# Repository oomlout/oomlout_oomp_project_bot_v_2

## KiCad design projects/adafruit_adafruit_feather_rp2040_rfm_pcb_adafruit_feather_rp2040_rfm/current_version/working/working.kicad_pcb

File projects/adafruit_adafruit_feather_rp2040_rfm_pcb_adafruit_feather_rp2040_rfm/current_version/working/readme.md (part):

# adafruit_feather_rp2040_rfm_pcb
 
## summary 
* id: adafruit_adafruit_feather_rp2040_rfm_pcb_adafruit_feather_rp2040_rfm
* user: adafruit
* name: adafruit_feather_rp2040_rfm_pcb
* board: adafruit_feather_rp2040_rfm
* repo: https://github.com/adafruit/Adafruit-Feather-RP2040-RFM-PCB

* src_file_repo_sch: 
* src_file_repo_sch_link: https://github.com/adafruit/Adafruit-Feather-RP2040-RFM-PCB/tree/main/
* full details link: https://github.com/oomlout/oomlout_oomp_project_bot_v_2/tree/main/projects/adafruit_adafruit_feather_rp2040_rfm_pcb_adafruit_feather_rp2040_rfm/current_version/working  

## schematic  
  
[schematic (pdf)](working_schematic.pdf) 

## pcb  

[board (pdf)](working.pdf)  

## working_bom
| Id | Designator | Footprint | Quantity | Designation | Supplier and ref |  | None | 
| --- | --- | --- | --- | --- | --- | --- | --- | 
| 1 | PLABEL18 | PLABEL18 | 1 |  |  |  | [''] | 
| 2 | C13,C9,C12,C6,C18,C7,C14 | _0402NO | 7 | 0.1uF |  |  | [''] | 
| 3 | Y1 | CRYSTAL_2.5X2 | 1 | 12MHz/12pF |  |  | [''] | 
| 4 | PLABEL19 | PLABEL19 | 1 |  |  |  | [''] | 
| 5 | L0 | CHIPLED_0603_NOOUTLINE | 1 | RED |  |  | [''] | 
| 6 | R11,R6 | _0402NO | 2 | 1K |  |  | [''] | 
| 7 | CHG0 | CHIPLED_0603_NOOUTLINE | 1 | ORANGE |  |  | [''] | 
| 8 | U1 | USON8_4X4 | 1 | 8MB QSPI |  |  | [''] | 
| 9 | PLABEL8 | PLABEL8 | 1 |  |  |  | [''] | 
| 10 | LED1 | SK6805_1515 | 1 | WS2812B_SK6805_1515 |  |  | [''] | 
| 11 | PLABEL2 | PLABEL2 | 1 |  |  |  | [''] | 
| 12 | R14,R15,R3,R2,R4,R7,R1,R5 | _0402NO | 8 | 10K |  |  | [''] | 
| 13 | PLABEL7 | PLABEL7 | 1 |  |  |  | [''] | 
| 14 | PLABEL4 | PLABEL4 | 1 |  |  |  | [''] | 
| 15 | R12,R13,R8 | _0402NO | 3 | 5.1K |  |  | [''] | 
| 16 | U2 | SOT23-5 | 1 | RT9080-3.3 |  |  | [''] | 
| 17 | PLABEL0 | PLABEL0 | 1 |  |  |  | [''] | 
| 18 | X1 | JSTPH2_BATT | 1 | JSTPH |  |  | [''] | 
| 19 | @HOLE0,@HOLE1 |  | 2 |  |  |  | [''] | 
| 20 | SW2,SW1 | BTN_RKB2_4.6X2.8 | 2 | KMR2 |  |  | [''] | 
| 21 | D4 | SOD-323F | 1 | PMEG2020AEA |  |  | [''] | 
| 22 | X6 | USB_C_CUSB31-CFM2AX-01-X | 1 | USB Type C |  |  | [''] | 
| 23 | C4,C20,C1,C5 | 0805-NO | 4 | 10uF |  |  | [''] | 
| 24 | U$31,U$32 | MOUNTINGHOLE_2.5_PLATED | 2 | MOUNTINGHOLE2.5 |  |  | [''] | 
| 25 | U3 | SOT23-5 | 1 | MCP73831T-2ACI/OT |  |  | [''] | 
| 26 | PLABEL16 | PLABEL16 | 1 |  |  |  | [''] | 
| 27 | PLABEL1 | PLABEL1 | 1 |  |  |  | [''] | 
| 28 | C8,C10,C15,C11,C17 | _0402NO | 5 | 1uF |  |  | [''] | 
| 29 | PLABEL5 | PLABEL5 | 1 |  |  |  | [''] | 
| 30 | PLABEL21 | PLABEL21 | 1 |  |  |  | [''] | 
| 31 | U$34,U$35 | FIDUCIAL_1MM | 2 | FIDUCIAL_1MM |  |  | [''] | 
| 32 | JP3 | 1X12_ROUND | 1 |  |  |  | [''] | 
| 33 | PLABEL22 | PLABEL22 | 1 |  |  |  | [''] | 
| 34 | PLABEL11 | PLABEL11 | 1 |  |  |  | [''] | 
| 35 | C3,C2 | _0402NO | 2 | 22pF |  |  | [''] | 
| 36 | PLABEL3 | PLABEL3 | 1 |  |  |  | [''] | 
| 37 | PLABEL6 | PLABEL6 | 1 |  |  |  | [''] | 
| 38 | PLABEL14 | PLABEL14 | 1 |  |  |  | [''] | 
| 39 | RFM1 | RFMHCW_SMT | 1 | RFM9x |  |  | [''] | 
| 40 | X2 | U.FL | 1 | uFL |  |  | [''] | 
| 41 | R10,R9 | _0402NO | 2 | 22 ohm |  |  | [''] | 
| 42 | JP1 | 1X16_ROUND | 1 |  |  |  | [''] | 
| 43 | PLABEL17 | PLABEL17 | 1 |  |  |  | [''] | 
| 44 | Q3 | DFN2015-3 | 1 | DMG3415UFY |  |  | [''] | 
| 45 | CONN1 | JST_SH4_RA | 1 | STEMMA_I2C_QTRA |  |  | [''] | 
| 46 | PLABEL12 | PLABEL12 | 1 |  |  |  | [''] | 
| 47 | PLABEL15 | PLABEL15 | 1 |  |  |  | [''] | 
| 48 | PLABEL20 | PLABEL20 | 1 |  |  |  | [''] | 
| 49 | PLABEL10 | PLABEL10 | 1 |  |  |  | [''] | 
| 50 | PLABEL9 | PLABEL9 | 1 |  |  |  | [''] | 
| 51 | PLABEL13 | PLABEL13 | 1 |  |  |  | [''] | 
| 52 | D3 | SOD-323F | 1 | 1N4148 |  |  | [''] | 
| 53 | JP4 | 1X01_ROUND | 1 |  |  |  | [''] | 
| 54 | IC1 | QFN56_7MM_REDUCEDEPAD | 1 | RP2040_QFN56 |  |  | [''] | 
| 55 | PLABEL25 | PLABEL25 | 1 |  |  |  | [''] | 
| 56 | PLABEL35 | PLABEL35 | 1 |  |  |  | [''] | 
| 57 | PLABEL53 | PLABEL53 | 1 |  |  |  | [''] | 
| 58 | PLABEL40 | PLABEL40 | 1 |  |  |  | [''] | 
| 59 | PLABEL45 | PLABEL45 | 1 |  |  |  | [''] | 
| 60 | U$46 | STEMMAQT | 1 |  |  |  | [''] | 
| 61 | U$47 | FEATHERLOGO_SMALL | 1 |  |  |  | [''] | 
| 62 | PLABEL47 | PLABEL47 | 1 |  |  |  | [''] | 
| 63 | PLABEL24,PLABEL54 | PLABEL24 | 2 |  |  |  | [''] | 
| 64 | PLABEL46 | PLABEL46 | 1 |  |  |  | [''] | 
| 65 | PLABEL33 | PLABEL33 | 1 |  |  |  | [''] | 
| 66 | PLABEL52 | PLABEL52 | 1 |  |  |  | [''] | 
| 67 | PLABEL49 | PLABEL49 | 1 |  |  |  | [''] | 
| 68 | PLABEL27 | PLABEL27 | 1 |  |  |  | [''] | 
| 69 | PLABEL540 | PLABEL540 | 1 |  |  |  | [''] | 
| 70 | PLABEL32 | PLABEL32 | 1 |  |  |  | [''] | 
| 71 | PLABEL30 | PLABEL30 | 1 |  |  |  | [''] | 
| 72 | PLABEL38 | PLABEL38 | 1 |  |  |  | [''] | 
| 73 | PLABEL41 | PLABEL41 | 1 |  |  |  | [''] | 
| 74 | PLABEL44 | PLABEL44 | 1 |  |  |  | [''] | 
| 75 | PLABEL34 | PLABEL34 | 1 |  |  |  | [''] | 
| 76 | PLABEL29 | PLABEL29 | 1 |  |  |  | [''] | 
| 77 | PLABEL51 | PLABEL51 | 1 |  |  |  | [''] | 
| 78 | PLABEL36 | PLABEL36 | 1 |  |  |  | [''] | 
| 79 | PLABEL42 | PLABEL42 | 1 |  |  |  | [''] | 
| 80 | PLABEL39 | PLABEL39 | 1 |  |  |  | [''] | 
| 81 | PLABEL43 | PLABEL43 | 1 |  |  |  | [''] | 
| 82 | U$13 | PCBFEAT-REV-040 | 1 |  |  |  | [''] | 
| 83 | U$45 | ADAFRUIT_5MM | 1 |  |  |  | [''] | 
| 84 | PLABEL31 | PLABEL31 | 1 |  |  |  | [''] | 
| 85 | PLABEL26 | PLABEL26 | 1 |  |  |  | [''] | 
| 86 | D-1,D+1 | B1,27 | 2 | TPB1,27 |  |  | [''] | 
| 87 | PLABEL28 | PLABEL28 | 1 |  |  |  | [''] | 
| 88 | PLABEL48 | PLABEL48 | 1 |  |  |  | [''] | 
| 89 | PLABEL37 | PLABEL37 | 1 |  |  |  | [''] | 
| 90 | TP3 | TESTPOINT_ROUND_1.5MM_NO | 1 |  |  |  | [''] | 
| 91 | PLABEL23 | PLABEL23 | 1 |  |  |  | [''] | 

## bom_schematic
| Ref | Qnty | Value | Cmp name | Footprint | Description | Vendor | DNP | 
| --- | --- | --- | --- | --- | --- | --- | --- | 
| C1, C4, C5, C20 | 4 | 10uF | CAP_CERAMIC0805-NOOUTLINE | working:0805-NO |  |  |  | 
| C2, C3 | 2 | 22pF | CAP_CERAMIC_0402NO | working:_0402NO |  |  |  | 
| C6, C7, C9, C12, C13, C14, C18 | 7 | 0.1uF | CAP_CERAMIC_0402NO | working:_0402NO |  |  |  | 
| C8, C10, C11, C15, C17 | 5 | 1uF | CAP_CERAMIC_0402NO | working:_0402NO |  |  |  | 
| CHG0 | 1 | ORANGE | LED0603_NOOUTLINE | working:CHIPLED_0603_NOOUTLINE |  |  |  | 
| CONN1 | 1 | STEMMA_I2C_QTRA | STEMMA_I2C_QTRA | working:JST_SH4_RA |  |  |  | 
| D3 | 1 | 1N4148 | DIODESOD-323F | working:SOD-323F |  |  |  | 
| D4 | 1 | PMEG2020AEA | DIODESOD-323F | working:SOD-323F |  |  |  | 
| D+1 | 1 | TPB1,27 | TPB1,27 | working:B1,27 |  |  |  | 
| D-1 | 1 | TPB1,27 | TPB1,27 | working:B1,27 |  |  |  | 
| IC1 | 1 | RP2040_QFN56 | RP2040_QFN56 | working:QFN56_7MM_REDUCEDEPAD |  |  |  | 
| JP1 | 1 | HEADER-1X16ROUND | HEADER-1X16ROUND | working:1X16_ROUND |  |  |  | 
| JP3 | 1 | HEADER-1X12 | HEADER-1X12 | working:1X12_ROUND |  |  |  | 
| JP4 | 1 | HEADER-1X1ROUND | HEADER-1X1ROUND | working:1X01_ROUND |  |  |  | 
| L0 | 1 | RED | LED0603_NOOUTLINE | working:CHIPLED_0603_NOOUTLINE |  |  |  | 
| LED1 | 1 | WS2812B_SK6805_1515 | WS2812B_SK6805_1515 | working:SK6805_1515 |  |  |  | 
| Q3 | 1 | DMG3415UFY | MOSFET-P_DFN2015 | working:DFN2015-3 |  |  |  | 
| R1, R2, R3, R4, R5, R7, R14, R15 | 8 | 10K | RESISTOR_0402NO | working:_0402NO |  |  |  | 
| R6, R11 | 2 | 1K | RESISTOR_0402NO | working:_0402NO |  |  |  | 
| R8, R12, R13 | 3 | 5.1K | RESISTOR_0402NO | working:_0402NO |  |  |  | 
| R9, R10 | 2 | 22 ohm | RESISTOR_0402NO | working:_0402NO |  |  |  | 
| RFM1 | 1 | RFM9x | RFM69HCW_SMT | working:RFMHCW_SMT |  |  |  | 
| SW1, SW2 | 2 | KMR2 | SWITCH_TACT_SMT_RKB2 | working:BTN_RKB2_4.6X2.8 |  |  |  | 
| TP3 | 1 | TESTPOINTROUND1.5MMNO | TESTPOINTROUND1.5MMNO | working:TESTPOINT_ROUND_1.5MM_NO |  |  |  | 
| U1 | 1 | 8MB QSPI | SPIFLASH_8PIN_4X4 | working:USON8_4X4 |  |  |  | 
| U2 | 1 | RT9080-3.3 | VREG_SOT23-5 | working:SOT23-5 |  |  |  | 
| U3 | 1 | MCP73831T-2ACI/OT | MCP73831/2 | working:SOT23-5 |  |  |  | 
| U$31, U$32 | 2 | MOUNTINGHOLE2.5 | MOUNTINGHOLE2.5 | working:MOUNTINGHOLE_2.5_PLATED |  |  |  | 
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
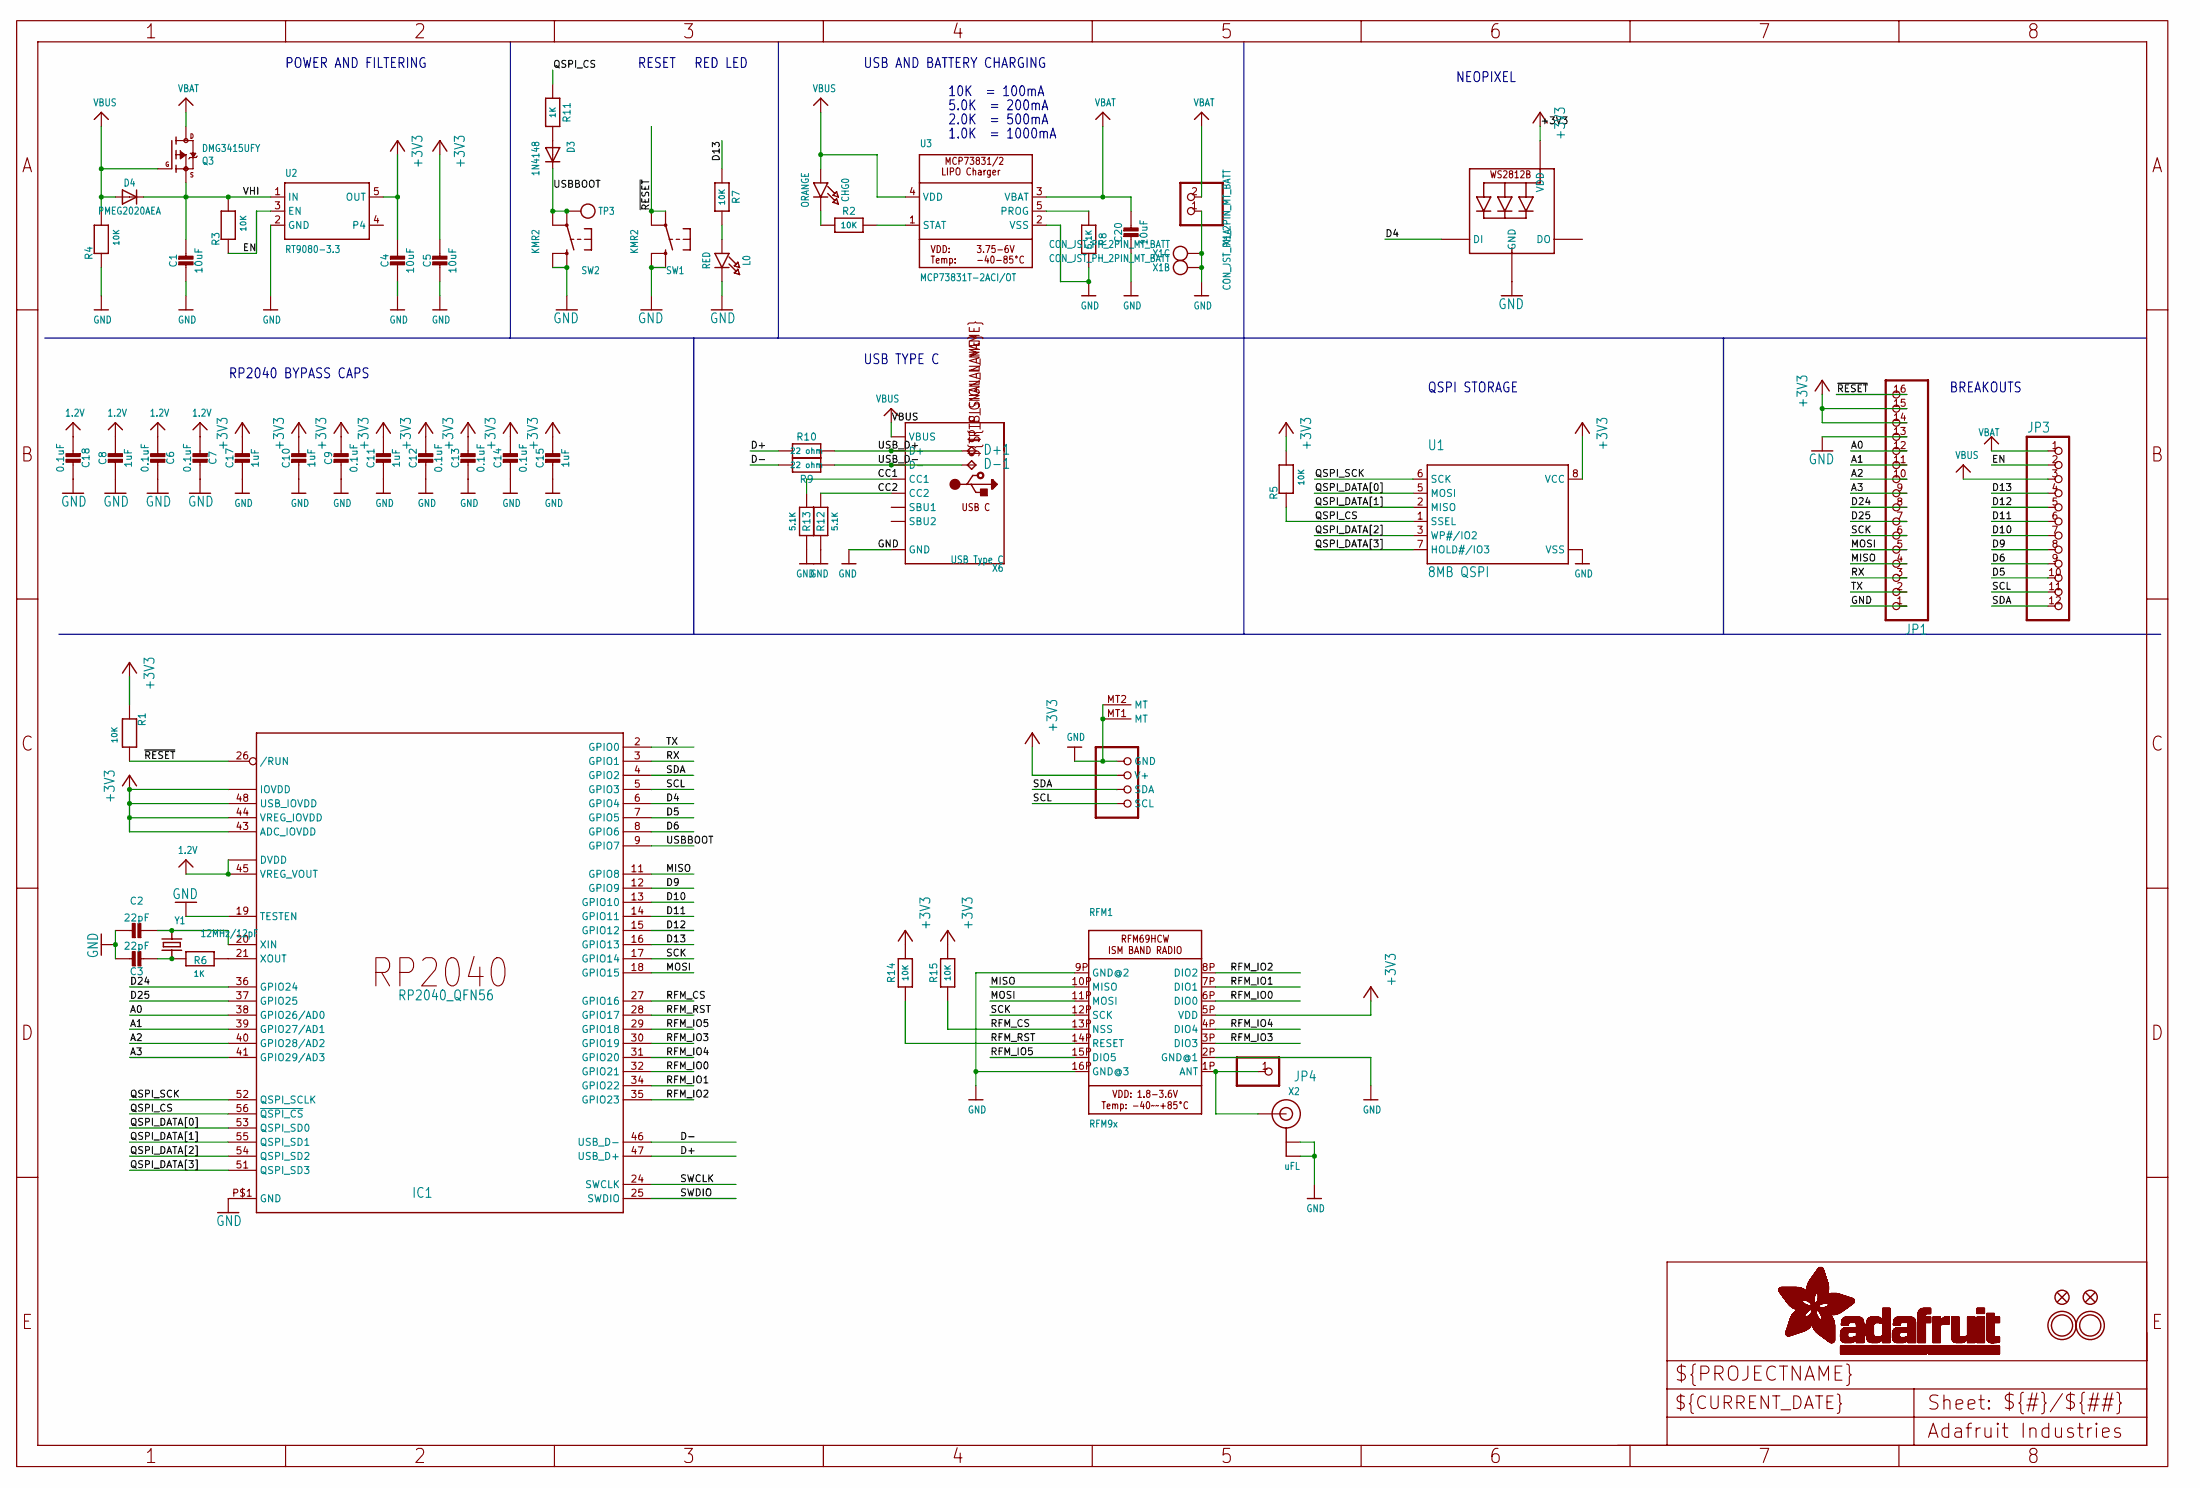
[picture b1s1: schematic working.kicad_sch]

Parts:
C1, C4, C5, C20: 10uF; 0805-NO
C2, C3: 22pF; _0402NO
C6, C7, C9, C12, C13, C14, C18: 0.1uF; _0402NO
C8, C10, C11, C15, C17: 1uF; _0402NO
CHG0: ORANGE; CHIPLED_0603_NOOUTLINE
CONN1: STEMMA_I2C_QTRA; JST_SH4_RA
D3: 1N4148; SOD-323F
D4: PMEG2020AEA; SOD-323F
D+1: TPB1,27; B1,27
D-1: TPB1,27; B1,27
IC1: RP2040_QFN56; QFN56_7MM_REDUCEDEPAD
JP1: HEADER-1X16ROUND; 1X16_ROUND
JP3: HEADER-1X12; 1X12_ROUND
JP4: HEADER-1X1ROUND; 1X01_ROUND
L0: RED; CHIPLED_0603_NOOUTLINE
LED1: WS2812B_SK6805_1515; SK6805_1515
Q3: DMG3415UFY; DFN2015-3
R1, R2, R3, R4, R5, R7, R14, R15: 10K; _0402NO
R6, R11: 1K; _0402NO
R8, R12, R13: 5.1K; _0402NO
R9, R10: 22 ohm; _0402NO
RFM1: RFM9x; RFMHCW_SMT
SW1, SW2: KMR2; BTN_RKB2_4.6X2.8
TP3: TESTPOINTROUND1.5MMNO; TESTPOINT_ROUND_1.5MM_NO
U1: 8MB QSPI; USON8_4X4
U2: RT9080-3.3; SOT23-5; JLC_ROTATION 0
U3: MCP73831T-2ACI/OT; SOT23-5
U$31, U$32: MOUNTINGHOLE2.5; MOUNTINGHOLE_2.5_PLATED
U$34, U$35: FIDUCIAL_1MM
X1: CON_JST_PH_2PIN_MT_BATT; JSTPH2_BATT
X2: uFL; U.FL
X6: USB Type C; USB_C_CUSB31-CFM2AX-01-X
Y1: 12MHz/12pF; CRYSTAL_2.5X2

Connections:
1.2V: C6.2, C7.2, C8.1, C18.2, IC1.23 (DVDD), IC1.45 (VREG_VOUT), IC1.50 (DVDD)
+3V3: C4.1, C5.1, C9.1, C10.1, C11.1, C12.1, C13.1, C14.1, C15.1, C17.1, CONN1.2 (V+), IC1.1 (IOVDD), IC1.10 (IOVDD), IC1.22 (IOVDD), IC1.33 (IOVDD), IC1.42 (IOVDD), IC1.43 (ADC_IOVDD), IC1.44 (VREG_IOVDD), IC1.48 (USB_IOVDD), IC1.49 (IOVDD), JP1.14, JP1.15, LED1.2 (VDD), R1.1, R5.2, R14.2, R15.2, RFM1.5P (VDD), U1.8 (VCC), U2.5 (OUT)
A0: IC1.38 (GPIO26/AD0), JP1.12
A1: IC1.39 (GPIO27/AD1), JP1.11
A2: IC1.40 (GPIO28/AD2), JP1.10
A3: IC1.41 (GPIO29/AD3), JP1.9
CC1: R13.2, X6.A5 (CC1)
CC2: R12.2, X6.B5 (CC2)
D4: IC1.6 (GPIO4), LED1.1 (DI)
D5: IC1.7 (GPIO5), JP3.10
D6: IC1.8 (GPIO6), JP3.9
D9: IC1.12 (GPIO9), JP3.8
D10: IC1.13 (GPIO10), JP3.7
D11: IC1.14 (GPIO11), JP3.6
D12: IC1.15 (GPIO12), JP3.5
D13: IC1.16 (GPIO13), JP3.4, R7.1
D24: IC1.36 (GPIO24), JP1.8
D25: IC1.37 (GPIO25), JP1.7
D+: IC1.47 (USB_D+), R10.2
D-: IC1.46 (USB_D-), R9.2
EN: JP3.2, R3.1, U2.3 (EN)
GND: C1.2, C2.1, C3.1, C4.2, C5.2, C6.1, C7.1, C8.2, C9.2, C10.2, C11.2, C12.2, C13.2, C14.2, C15.2, C17.2, C18.1, C20.2, CONN1.1 (GND), CONN1.MT1 (MT), CONN1.MT2 (MT), IC1.19 (TESTEN), IC1.P$1 (GND), JP1.1, JP1.13, L0.C, LED1.4 (GND), R4.1, R8.2, R12.1, R13.1, RFM1.2P (GND@1), RFM1.9P (GND@2), RFM1.16P (GND@3), SW1.B (S), SW1.B' (S1), SW2.B (S), SW2.B' (S1), U1.4 (VSS), U1.PAD (VSS), U2.2 (GND), U3.2 (VSS), X1.1, X1.NC1, X1.NC2, X2.1 (GND@0), X2.2 (GND@1), X6.A1B12 (GND), X6.B1A12 (GND)
MISO: IC1.11 (GPIO8), JP1.4, RFM1.10P (MISO)
MOSI: IC1.18 (GPIO15), JP1.5, RFM1.11P (MOSI)
unnamed: CHG0.C, R2.1
unnamed: L0.A, R7.2
unnamed: R2.2, U3.1 (STAT)
unnamed: R8.1, U3.5 (PROG)
unnamed: C2.2, IC1.20 (XIN), Y1.3 (2)
unnamed: C3.2, R6.1, Y1.1
unnamed: IC1.21 (XOUT), R6.2
unnamed: D3.A, R11.2
QSPI_CS: IC1.56 (~QSPI_CS), R5.1, R11.1, U1.1 (SSEL)
QSPI_DATA[0]: IC1.53 (QSPI_SD0), U1.5 (MOSI)
QSPI_DATA[1]: IC1.55 (QSPI_SD1), U1.2 (MISO)
QSPI_DATA[2]: IC1.54 (QSPI_SD2), U1.3 (WP#/IO2)
QSPI_DATA[3]: IC1.51 (QSPI_SD3), U1.7 (HOLD#/IO3)
QSPI_SCK: IC1.52 (QSPI_SCLK), U1.6 (SCK)
RFM_CS: IC1.27 (GPIO16), R15.1, RFM1.13P (NSS)
RFM_IO0: IC1.32 (GPIO21), RFM1.6P (DIO0)
RFM_IO1: IC1.34 (GPIO22), RFM1.7P (DIO1)
RFM_IO2: IC1.35 (GPIO23), RFM1.8P (DIO2)
RFM_IO3: IC1.30 (GPIO19), RFM1.3P (DIO3)
RFM_IO4: IC1.31 (GPIO20), RFM1.4P (DIO4)
RFM_IO5: IC1.29 (GPIO18), RFM1.15P (DIO5)
RFM_RST: IC1.28 (GPIO17), R14.1, RFM1.14P (RESET)
RFOUT: JP4.1, RFM1.1P (ANT), X2.3 (SIGNAL)
RX: IC1.3 (GPIO1), JP1.3
SCK: IC1.17 (GPIO14), JP1.6, RFM1.12P (SCK)
SCL: CONN1.4 (SCL), IC1.5 (GPIO3), JP3.11
SDA: CONN1.3 (SDA), IC1.4 (GPIO2), JP3.12
SWCLK: IC1.24 (SWCLK)
SWDIO: IC1.25 (SWDIO)
TX: IC1.2 (GPIO0), JP1.2
USBBOOT: D3.C, IC1.9 (GPIO7), SW2.A, SW2.A' (P1), TP3.P$1
USB_D+: D+1.TP, R10.1, X6.A6 (D+), X6.B6 (D+)
USB_D-: D-1.TP, R9.1, X6.A7 (D-), X6.B7 (D-)
VBAT: C20.1, JP3.1, Q3.3 (D), U3.3 (VBAT), X1.2
VBUS: CHG0.A, D4.A, JP3.3, Q3.1 (G), R4.2, U3.4 (VDD), X6.A4B9 (VBUS), X6.B4A9 (VBUS)
VHI: C1.1, D4.C, Q3.2 (S), R3.2, U2.1 (IN)
~RESET: IC1.26 (/RUN), JP1.16, R1.2, SW1.A, SW1.A' (P1)

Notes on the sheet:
USB AND BATTERY CHARGING
RP2040 BYPASS CAPS
RED LED
QSPI STORAGE
RESET
1.0K = 1000mA
NEOPIXEL
10K = 100mA
POWER AND FILTERING
BREAKOUTS
2.0K = 500mA
5.0K = 200mA
USB TYPE C

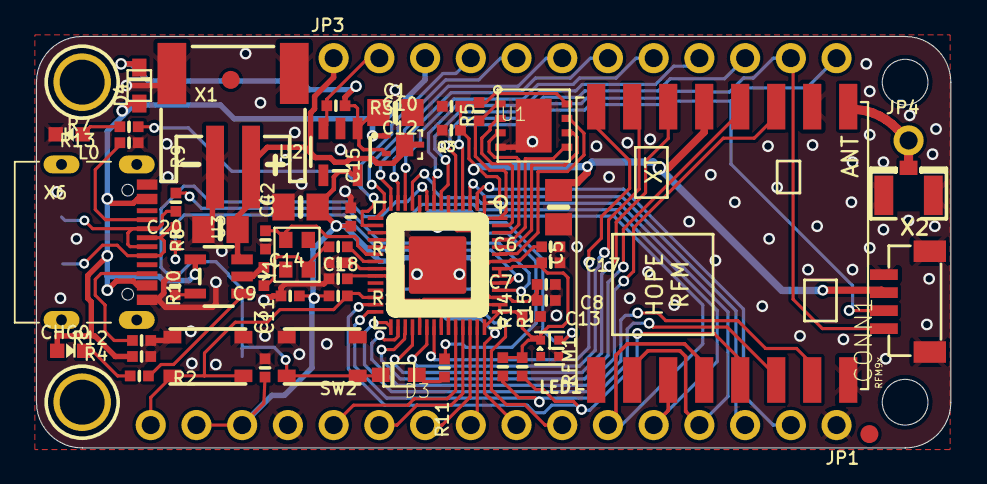
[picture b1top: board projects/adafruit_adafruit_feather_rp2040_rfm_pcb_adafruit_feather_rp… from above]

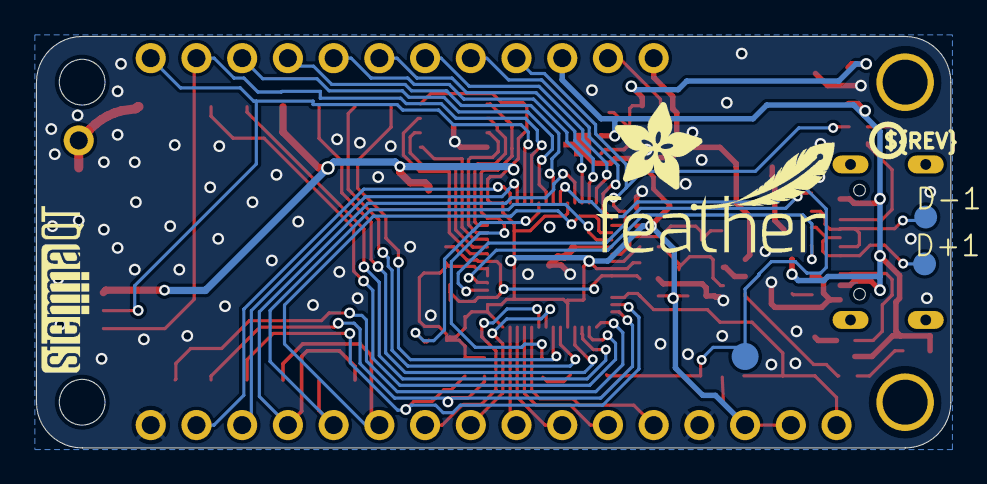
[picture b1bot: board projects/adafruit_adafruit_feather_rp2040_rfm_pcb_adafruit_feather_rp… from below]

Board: 2 copper layers, 50.8 x 22.9 mm, 122 parts (39 on the bottom side), 59 nets.

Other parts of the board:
@HOLE0, @HOLE1: (no value)
PLABEL0: PLABEL0
PLABEL1: PLABEL1
PLABEL2: PLABEL2
PLABEL3: PLABEL3
PLABEL4: PLABEL4
PLABEL5: PLABEL5
PLABEL6: PLABEL6
PLABEL7: PLABEL7
PLABEL8: PLABEL8
PLABEL9: PLABEL9
PLABEL10: PLABEL10
PLABEL11: PLABEL11
PLABEL12: PLABEL12
PLABEL13: PLABEL13
PLABEL14: PLABEL14
PLABEL15: PLABEL15
PLABEL16: PLABEL16
PLABEL17: PLABEL17
PLABEL18: PLABEL18
PLABEL19: PLABEL19
PLABEL20: PLABEL20
PLABEL21: PLABEL21
PLABEL22: PLABEL22
PLABEL23: PLABEL23
PLABEL24, PLABEL54: PLABEL24
PLABEL25: PLABEL25
PLABEL26: PLABEL26
PLABEL27: PLABEL27
PLABEL28: PLABEL28
PLABEL29: PLABEL29
PLABEL30: PLABEL30
PLABEL31: PLABEL31
PLABEL32: PLABEL32
PLABEL33: PLABEL33
PLABEL34: PLABEL34
PLABEL35: PLABEL35
PLABEL36: PLABEL36
PLABEL37: PLABEL37
PLABEL38: PLABEL38
PLABEL39: PLABEL39
PLABEL40: PLABEL40
PLABEL41: PLABEL41
PLABEL42: PLABEL42
PLABEL43: PLABEL43
PLABEL44: PLABEL44
PLABEL45: PLABEL45
PLABEL46: PLABEL46
PLABEL47: PLABEL47
PLABEL48: PLABEL48
PLABEL49: PLABEL49
PLABEL51: PLABEL51
PLABEL52: PLABEL52
PLABEL53: PLABEL53
PLABEL540: PLABEL540
U$13: PCBFEAT-REV-040
U$45: ADAFRUIT_5MM
U$46: STEMMAQT
U$47: FEATHERLOGO_SMALL

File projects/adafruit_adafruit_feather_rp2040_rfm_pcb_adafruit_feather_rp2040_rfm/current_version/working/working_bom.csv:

"Id";"Designator";"Footprint";"Quantity";"Designation";"Supplier and ref";
1;"PLABEL18";"PLABEL18";1;"";;;
2;"C13,C9,C12,C6,C18,C7,C14";"_0402NO";7;"0.1uF";;;
3;"Y1";"CRYSTAL_2.5X2";1;"12MHz/12pF";;;
4;"PLABEL19";"PLABEL19";1;"";;;
5;"L0";"CHIPLED_0603_NOOUTLINE";1;"RED";;;
6;"R11,R6";"_0402NO";2;"1K";;;
7;"CHG0";"CHIPLED_0603_NOOUTLINE";1;"ORANGE";;;
8;"U1";"USON8_4X4";1;"8MB QSPI";;;
9;"PLABEL8";"PLABEL8";1;"";;;
10;"LED1";"SK6805_1515";1;"WS2812B_SK6805_1515";;;
11;"PLABEL2";"PLABEL2";1;"";;;
12;"R14,R15,R3,R2,R4,R7,R1,R5";"_0402NO";8;"10K";;;
13;"PLABEL7";"PLABEL7";1;"";;;
14;"PLABEL4";"PLABEL4";1;"";;;
15;"R12,R13,R8";"_0402NO";3;"5.1K";;;
16;"U2";"SOT23-5";1;"RT9080-3.3";;;
17;"PLABEL0";"PLABEL0";1;"";;;
18;"X1";"JSTPH2_BATT";1;"JSTPH";;;
19;"@HOLE0,@HOLE1";"";2;"";;;
20;"SW2,SW1";"BTN_RKB2_4.6X2.8";2;"KMR2";;;
21;"D4";"SOD-323F";1;"PMEG2020AEA";;;
22;"X6";"USB_C_CUSB31-CFM2AX-01-X";1;"USB Type C";;;
23;"C4,C20,C1,C5";"0805-NO";4;"10uF";;;
24;"U$31,U$32";"MOUNTINGHOLE_2.5_PLATED";2;"MOUNTINGHOLE2.5";;;
25;"U3";"SOT23-5";1;"MCP73831T-2ACI/OT";;;
26;"PLABEL16";"PLABEL16";1;"";;;
27;"PLABEL1";"PLABEL1";1;"";;;
28;"C8,C10,C15,C11,C17";"_0402NO";5;"1uF";;;
29;"PLABEL5";"PLABEL5";1;"";;;
30;"PLABEL21";"PLABEL21";1;"";;;
31;"U$34,U$35";"FIDUCIAL_1MM";2;"FIDUCIAL_1MM";;;
32;"JP3";"1X12_ROUND";1;"";;;
33;"PLABEL22";"PLABEL22";1;"";;;
34;"PLABEL11";"PLABEL11";1;"";;;
35;"C3,C2";"_0402NO";2;"22pF";;;
36;"PLABEL3";"PLABEL3";1;"";;;
37;"PLABEL6";"PLABEL6";1;"";;;
38;"PLABEL14";"PLABEL14";1;"";;;
39;"RFM1";"RFMHCW_SMT";1;"RFM9x";;;
40;"X2";"U.FL";1;"uFL";;;
41;"R10,R9";"_0402NO";2;"22 ohm";;;
42;"JP1";"1X16_ROUND";1;"";;;
43;"PLABEL17";"PLABEL17";1;"";;;
44;"Q3";"DFN2015-3";1;"DMG3415UFY";;;
45;"CONN1";"JST_SH4_RA";1;"STEMMA_I2C_QTRA";;;
46;"PLABEL12";"PLABEL12";1;"";;;
47;"PLABEL15";"PLABEL15";1;"";;;
48;"PLABEL20";"PLABEL20";1;"";;;
49;"PLABEL10";"PLABEL10";1;"";;;
50;"PLABEL9";"PLABEL9";1;"";;;
51;"PLABEL13";"PLABEL13";1;"";;;
52;"D3";"SOD-323F";1;"1N4148";;;
53;"JP4";"1X01_ROUND";1;"";;;
54;"IC1";"QFN56_7MM_REDUCEDEPAD";1;"RP2040_QFN56";;;
55;"PLABEL25";"PLABEL25";1;"";;;
56;"PLABEL35";"PLABEL35";1;"";;;
57;"PLABEL53";"PLABEL53";1;"";;;
58;"PLABEL40";"PLABEL40";1;"";;;
59;"PLABEL45";"PLABEL45";1;"";;;
60;"U$46";"STEMMAQT";1;"";;;
61;"U$47";"FEATHERLOGO_SMALL";1;"";;;
62;"PLABEL47";"PLABEL47";1;"";;;
63;"PLABEL24,PLABEL54";"PLABEL24";2;"";;;
64;"PLABEL46";"PLABEL46";1;"";;;
65;"PLABEL33";"PLABEL33";1;"";;;
66;"PLABEL52";"PLABEL52";1;"";;;
67;"PLABEL49";"PLABEL49";1;"";;;
68;"PLABEL27";"PLABEL27";1;"";;;
69;"PLABEL540";"PLABEL540";1;"";;;
70;"PLABEL32";"PLABEL32";1;"";;;
71;"PLABEL30";"PLABEL30";1;"";;;
72;"PLABEL38";"PLABEL38";1;"";;;
73;"PLABEL41";"PLABEL41";1;"";;;
74;"PLABEL44";"PLABEL44";1;"";;;
75;"PLABEL34";"PLABEL34";1;"";;;
76;"PLABEL29";"PLABEL29";1;"";;;
77;"PLABEL51";"PLABEL51";1;"";;;
78;"PLABEL36";"PLABEL36";1;"";;;
79;"PLABEL42";"PLABEL42";1;"";;;
80;"PLABEL39";"PLABEL39";1;"";;;
81;"PLABEL43";"PLABEL43";1;"";;;
82;"U$13";"PCBFEAT-REV-040";1;"";;;
83;"U$45";"ADAFRUIT_5MM";1;"";;;
84;"PLABEL31";"PLABEL31";1;"";;;
85;"PLABEL26";"PLABEL26";1;"";;;
86;"D-1,D+1";"B1,27";2;"TPB1,27";;;
87;"PLABEL28";"PLABEL28";1;"";;;
88;"PLABEL48";"PLABEL48";1;"";;;
89;"PLABEL37";"PLABEL37";1;"";;;
90;"TP3";"TESTPOINT_ROUND_1.5MM_NO";1;"";;;
91;"PLABEL23";"PLABEL23";1;"";;;

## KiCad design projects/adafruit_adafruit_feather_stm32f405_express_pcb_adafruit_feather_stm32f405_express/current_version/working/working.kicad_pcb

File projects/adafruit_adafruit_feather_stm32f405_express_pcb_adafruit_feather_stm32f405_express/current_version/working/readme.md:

# adafruit_feather_stm32f405_express_pcb
 
## summary 
* id: adafruit_adafruit_feather_stm32f405_express_pcb_adafruit_feather_stm32f405_express
* user: adafruit
* name: adafruit_feather_stm32f405_express_pcb
* board: adafruit_feather_stm32f405_express
* repo: https://github.com/adafruit/Adafruit-Feather-STM32F405-Express-PCB

* src_file_repo_sch: 
* src_file_repo_sch_link: https://github.com/adafruit/Adafruit-Feather-STM32F405-Express-PCB/tree/master/
* full details link: https://github.com/oomlout/oomlout_oomp_project_bot_v_2/tree/main/projects/adafruit_adafruit_feather_stm32f405_express_pcb_adafruit_feather_stm32f405_express/current_version/working  

## schematic  
  
[schematic (pdf)](working_schematic.pdf) 

## pcb  

[board (pdf)](working.pdf)  

## working_bom
| Id | Designator | Footprint | Quantity | Designation | Supplier and ref |  | None | 
| --- | --- | --- | --- | --- | --- | --- | --- | 
| 1 | C5 | 0805-NO | 1 | 10uF |  |  | [''] | 
| 2 | R2 | 0603-NO | 1 | 1K |  |  | [''] | 
| 3 | C12,C13,C3,C9,C8,C6 | 0805-NO | 6 | 10ÂµF |  |  | [''] | 
| 4 | L0 | CHIPLED_0805_NOOUTLINE | 1 | RED |  |  | [''] | 
| 5 | C7,C16,C11,C10,C4,C14,C17 | 0603-NO | 7 | 1uF |  |  | [''] | 
| 6 | SW1 | BTN_KMR2_4.6X2.8 | 1 | KMR2 |  |  | [''] | 
| 7 | R5,R8,R6 | 0603-NO | 3 | 5.1K |  |  | [''] | 
| 8 | U1 | SOIC8_150MIL | 1 | 25Q16 |  |  | [''] | 
| 9 | X1 | JSTPH2 | 1 | JSTPH |  |  | [''] | 
| 10 | U$24 | FEATHER_STM32F405_TOP | 1 |  |  |  | [''] | 
| 11 | U2 | SOT23-5 | 1 | AP2112-3.3 |  |  | [''] | 
| 12 | FB2 | 0805-NO | 1 | ferrite |  |  | [''] | 
| 13 | U$32,U$31 | MOUNTINGHOLE_2.5_PLATED | 2 | MOUNTINGHOLE2.5 |  |  | [''] | 
| 14 | Q3 | SOT23-R | 1 | DMG3405 |  |  | [''] | 
| 15 | U$35,U$34,U$37,U$5 | FIDUCIAL_1MM | 4 | FIDUCIAL_1MM |  |  | [''] | 
| 16 | R7 | 0603-NO | 1 | 2.2K |  |  | [''] | 
| 17 | X6 | USB_C_CUSB31-CFM2AX-01-X | 1 |  |  |  | [''] | 
| 18 | JP1 | 1X16_ROUND | 1 |  |  |  | [''] | 
| 19 | R3 | 0603-NO | 1 | 10K |  |  | [''] | 
| 20 | C15,C1 | 0603-NO | 2 | 0.1uF |  |  | [''] | 
| 21 | C2 | RESPACK_4X0603 | 1 | 22pF |  |  | [''] | 
| 22 | JP3 | 1X12_ROUND | 1 |  |  |  | [''] | 
| 23 | CHG0 | CHIPLED_0805_NOOUTLINE | 1 | ORANGE |  |  | [''] | 
| 24 | R4,R10 | 0603-NO | 2 | 100K |  |  | [''] | 
| 25 | Y1 | CRYSTAL_2.5X2 | 1 | 12mhz |  |  | [''] | 
| 26 | CONN1 | JST_SH4 | 1 | STEMMA_I2C_QT |  |  | [''] | 
| 27 | U$3 | TQFP64 | 1 | STM32F405R |  |  | [''] | 
| 28 | R1 | RESPACK_4X0603_NO | 1 | 10K |  |  | [''] | 
| 29 | @HOLE1,@HOLE0 |  | 2 |  |  |  | [''] | 
| 30 | LED1 | LED3535 | 1 | WS2812B3535 |  |  | [''] | 
| 31 | X2 | XTAL3215 | 1 | 32.768 |  |  | [''] | 
| 32 | R9 | RESPACK_4X0603_NO | 1 | 100K |  |  | [''] | 
| 33 | U3 | SOT23-5 | 1 | MCP73831T-2ACI/OT |  |  | [''] | 
| 34 | D4 | SOD-123 | 1 | MBR054 |  |  | [''] | 
| 35 | D+0,D-0 | B1,27 | 2 | TPB1,27 |  |  | [''] | 
| 36 | X5 | MICROSD | 1 |  |  |  | [''] | 
| 37 | TP1,TP3,TP2 | TESTPOINT_ROUND_1.5MM | 3 |  |  |  | [''] | 
| 38 | U$13 | PCBFEAT-REV-040 | 1 |  |  |  | [''] | 
| 39 | U$40 | FEATHER_STM32F405_BOT | 1 |  |  |  | [''] | 
| 40 | X3 | 2X05_1.27MM_SMT | 1 |  |  |  | [''] | 

## bom_schematic
| Ref | Qnty | Value | Cmp name | Footprint | Description | Vendor | DNP | 
| --- | --- | --- | --- | --- | --- | --- | --- | 
| C1, C15 | 2 | 0.1uF | CAP_CERAMIC0603_NO | working:0603-NO |  |  |  | 
| C2 | 1 | 22pF | CAP_4PACK1206 | working:RESPACK_4X0603 |  |  |  | 
| C3, C6, C8, C9, C12, C13 | 6 | 10ÂµF | CAP_CERAMIC0805-NOOUTLINE | working:0805-NO |  |  |  | 
| C4, C7, C10, C11, C14, C16, C17 | 7 | 1uF | CAP_CERAMIC0603_NO | working:0603-NO |  |  |  | 
| C5 | 1 | 10uF | CAP_CERAMIC0805-NOOUTLINE | working:0805-NO |  |  |  | 
| CHG0 | 1 | ORANGE | LED0805_NOOUTLINE | working:CHIPLED_0805_NOOUTLINE |  |  |  | 
| CONN1 | 1 | STEMMA_I2C_QT | STEMMA_I2C_QT | working:JST_SH4 |  |  |  | 
| D4 | 1 | MBR054 | DIODE-SCHOTTKYSOD-123 | working:SOD-123 |  |  |  | 
| D+0 | 1 | TPB1,27 | TPB1,27 | working:B1,27 |  |  |  | 
| D-0 | 1 | TPB1,27 | TPB1,27 | working:B1,27 |  |  |  | 
| FB2 | 1 | ferrite | FERRITE-0805NO | working:0805-NO |  |  |  | 
| JP1 | 1 | HEADER-1X16ROUND | HEADER-1X16ROUND | working:1X16_ROUND |  |  |  | 
| JP3 | 1 | HEADER-1X12 | HEADER-1X12 | working:1X12_ROUND |  |  |  | 
| L0 | 1 | RED | LED0805_NOOUTLINE | working:CHIPLED_0805_NOOUTLINE |  |  |  | 
| LED1 | 1 | WS2812B3535 | WS2812B3535 | working:LED3535 |  |  |  | 
| Q3 | 1 | DMG3405 | MOSFET-P | working:SOT23-R |  |  |  | 
| R1 | 1 | 10K | RESISTOR_4PACK_NO | working:RESPACK_4X0603_NO |  |  |  | 
| R2 | 1 | 1K | RESISTOR_0603_NOOUT | working:0603-NO |  |  |  | 
| R3 | 1 | 10K | RESISTOR_0603_NOOUT | working:0603-NO |  |  |  | 
| R4, R10 | 2 | 100K | RESISTOR_0603_NOOUT | working:0603-NO |  |  |  | 
| R5, R6, R8 | 3 | 5.1K | RESISTOR_0603_NOOUT | working:0603-NO |  |  |  | 
| R7 | 1 | 2.2K | RESISTOR_0603_NOOUT | working:0603-NO |  |  |  | 
| R9 | 1 | 100K | RESISTOR_4PACK_NO | working:RESPACK_4X0603_NO |  |  |  | 
| SW1 | 1 | KMR2 | SWITCH_TACT_SMT4.6X2.8 | working:BTN_KMR2_4.6X2.8 |  |  |  | 
| TP1, TP2, TP3 | 3 | TESTPOINTROUND1.5MM | TESTPOINTROUND1.5MM | working:TESTPOINT_ROUND_1.5MM |  |  |  | 
| U1 | 1 | 25Q16 | SPIFLASH_8PIN | working:SOIC8_150MIL |  |  |  | 
| U2 | 1 | AP2112-3.3 | VREG_SOT23-5 | working:SOT23-5 |  |  |  | 
| U3 | 1 | MCP73831T-2ACI/OT | MCP73831/2 | working:SOT23-5 |  |  |  | 
| U$3 | 1 | STM32F405R | STM32F405R | working:TQFP64 |  |  |  | 
| U$5, U$34, U$35, U$37 | 4 | FIDUCIAL_1MM | FIDUCIAL_1MM | working:FIDUCIAL_1MM |  |  |  | 
| U$31, U$32 | 2 | MOUNTINGHOLE2.5 | MOUNTINGHOLE2.5 | working:MOUNTINGHOLE_2.5_PLATED |  |  |  | 
| X1 | 1 | JSTPH | CON_JST_PH_2PIN | working:JSTPH2 |  |  |  | 
| X2 | 1 | 32.768 | XTAL-3.2X1.5 | working:XTAL3215 |  |  |  | 
| X3 | 1 | JTAG-CORTEX | JTAG-CORTEX | working:2X05_1.27MM_SMT |  |  |  | 
| X5 | 1 | MICROSD | MICROSD | working:MICROSD |  |  |  | 
| X6 | 1 | USB_C | USB_C | working:USB_C_CUSB31-CFM2AX-01-X |  |  |  | 
| Y1 | 1 | 12mhz | CRYSTAL2.5X2.0 | working:CRYSTAL_2.5X2 |  |  |  | 

## mounting_holes
| x | y | package | value | ref | size | 
| --- | --- | --- | --- | --- | --- | 
| 0.0 | 17.78 | MOUNTINGHOLE_2.5_PLATED | MOUNTINGHOLE2.5 | U$31 | m3 | 
| 0.0 | 0.0 | MOUNTINGHOLE_2.5_PLATED | MOUNTINGHOLE2.5 | U$32 | m3 |

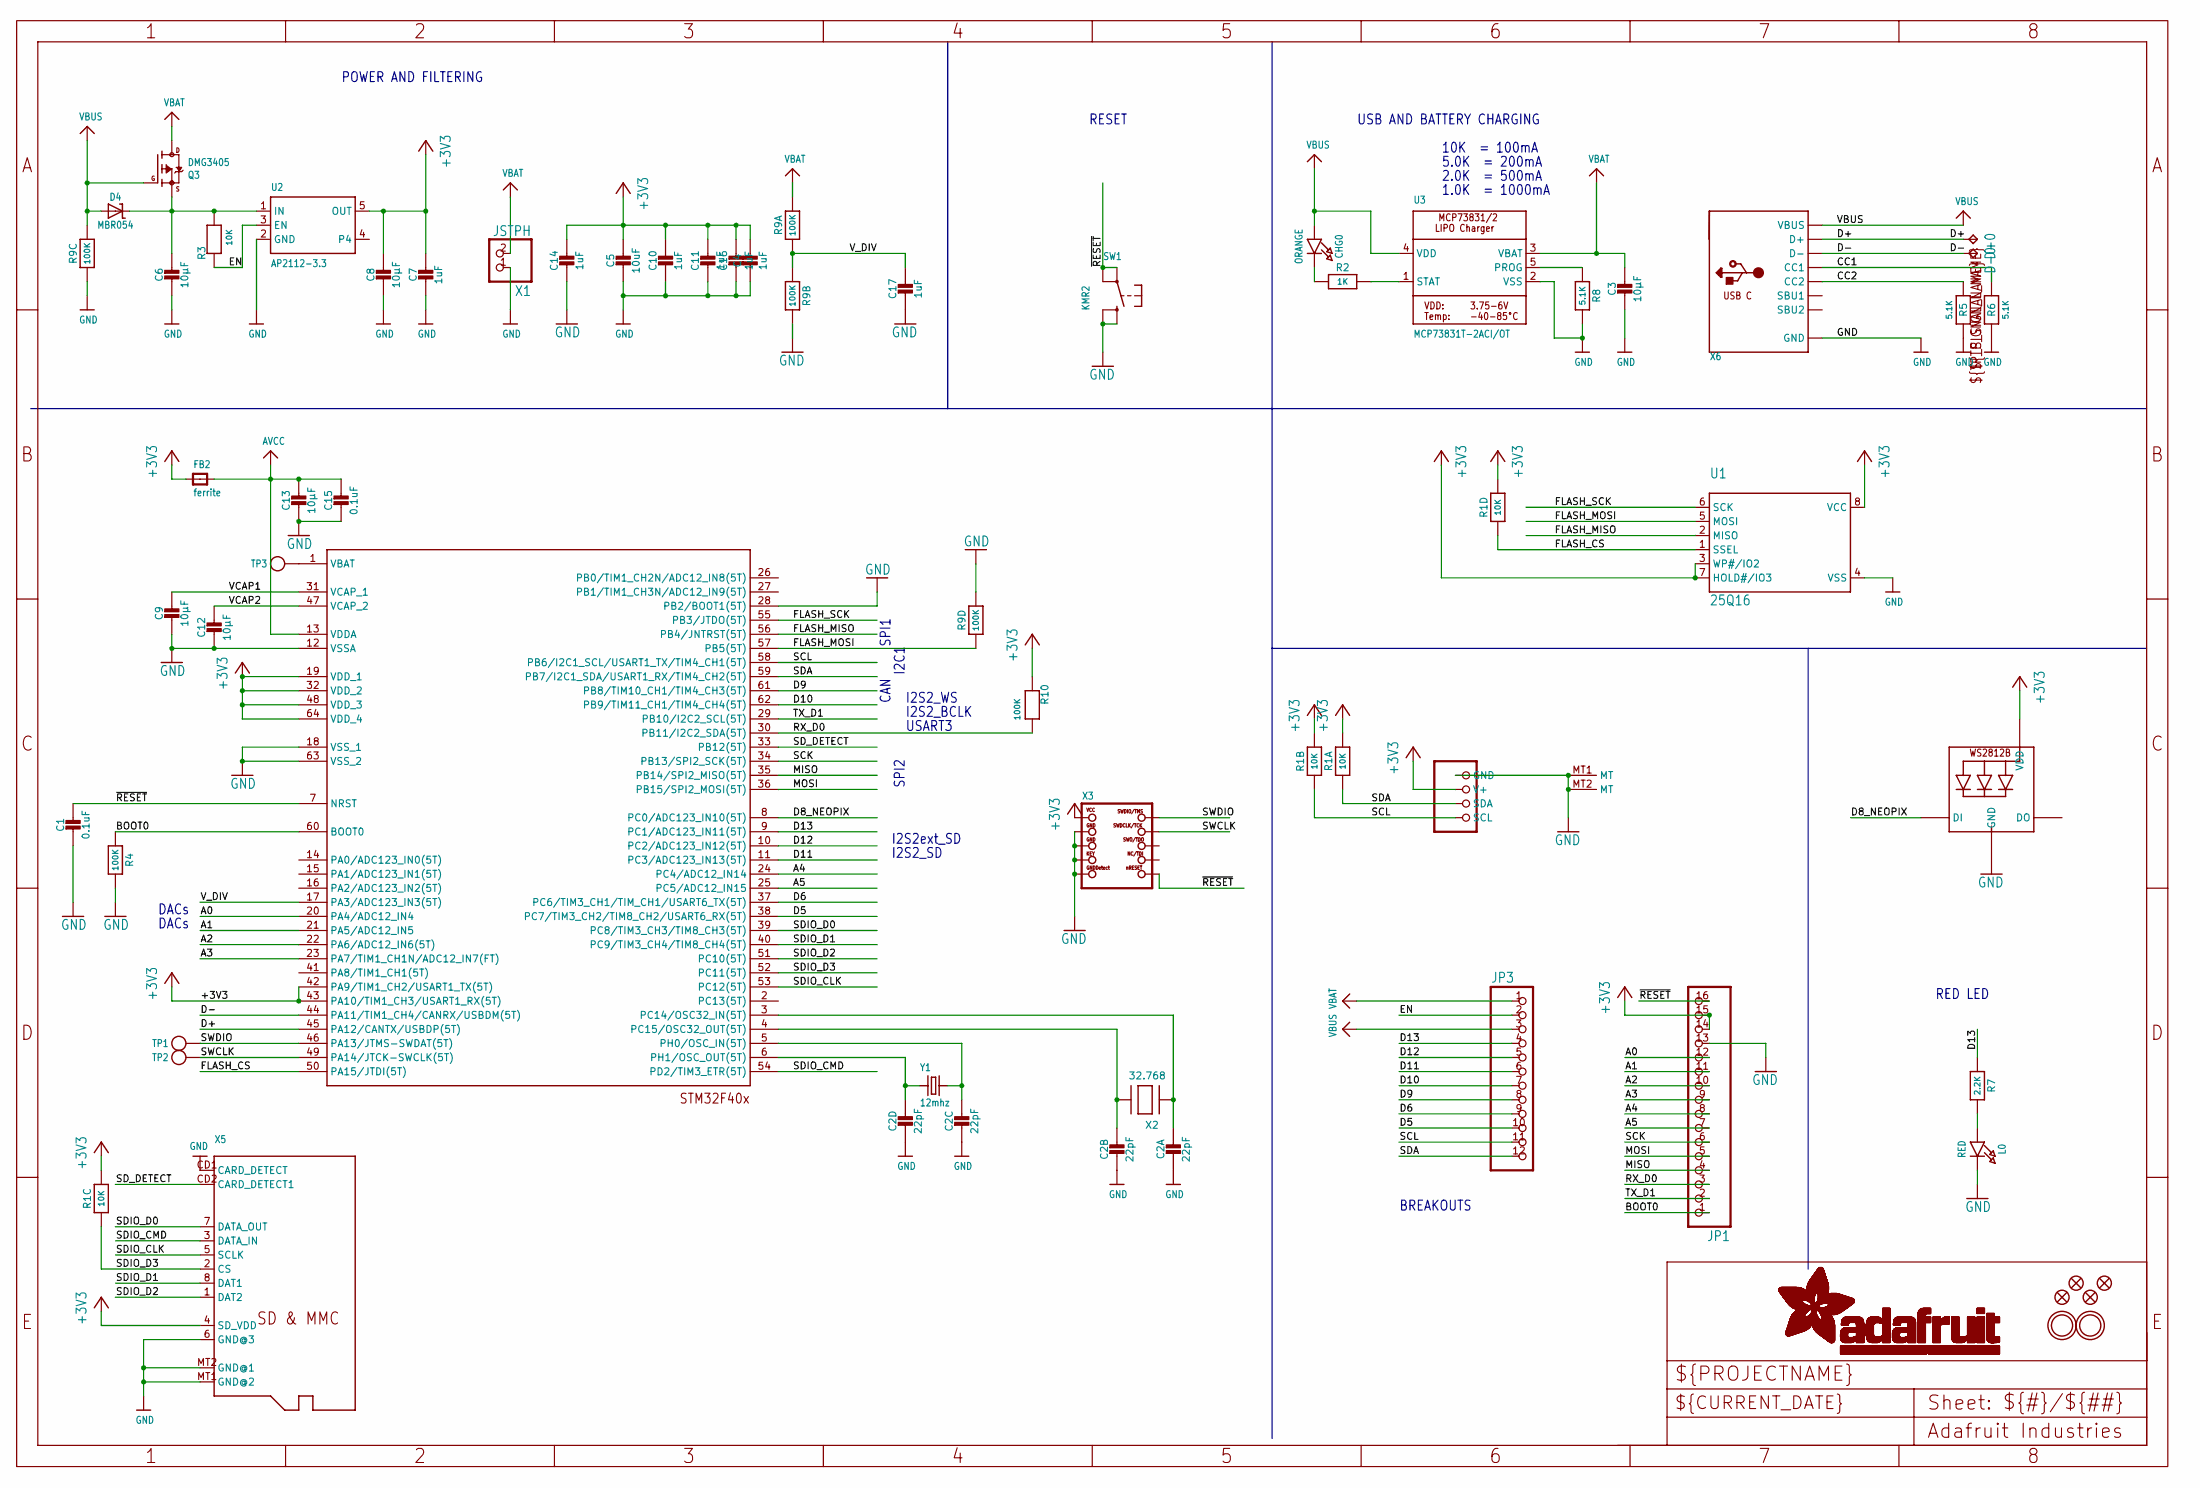
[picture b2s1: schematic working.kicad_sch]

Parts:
C1, C15: 0.1uF; 0603-NO
C2: 22pF; RESPACK_4X0603
C3, C6, C8, C9, C12, C13: 10µF; 0805-NO
C4, C7, C10, C11, C14, C16, C17: 1uF; 0603-NO
C5: 10uF; 0805-NO
CHG0: ORANGE; CHIPLED_0805_NOOUTLINE
CONN1: STEMMA_I2C_QT; JST_SH4
D4: MBR054; SOD-123
D+0: TPB1,27; B1,27
D-0: TPB1,27; B1,27
FB2: ferrite; 0805-NO
JP1: HEADER-1X16ROUND; 1X16_ROUND
JP3: HEADER-1X12; 1X12_ROUND
L0: RED; CHIPLED_0805_NOOUTLINE
LED1: WS2812B3535; LED3535
Q3: DMG3405; SOT23-R
R1: 10K; RESPACK_4X0603_NO
R2: 1K; 0603-NO
R3: 10K; 0603-NO
R4, R10: 100K; 0603-NO
R5, R6, R8: 5.1K; 0603-NO
R7: 2.2K; 0603-NO
R9: 100K; RESPACK_4X0603_NO
SW1: KMR2; BTN_KMR2_4.6X2.8
TP1, TP2, TP3: TESTPOINTROUND1.5MM; TESTPOINT_ROUND_1.5MM
U1: 25Q16; SOIC8_150MIL
U2: AP2112-3.3; SOT23-5
U3: MCP73831T-2ACI/OT; SOT23-5
U$3: STM32F405R; TQFP64
U$5, U$34, U$35, U$37: FIDUCIAL_1MM
U$31, U$32: MOUNTINGHOLE2.5; MOUNTINGHOLE_2.5_PLATED
X1: JSTPH; JSTPH2
X2: 32.768; XTAL3215
X3: JTAG-CORTEX; 2X05_1.27MM_SMT
X5: MICROSD
X6: USB_C; USB_C_CUSB31-CFM2AX-01-X
Y1: 12mhz; CRYSTAL_2.5X2

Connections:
+3V3: C4.1, C5.1, C7.1, C8.1, C10.1, C11.1, C14.1, C16.1, CONN1.2 (V+), FB2.1, JP1.14, JP1.15, LED1.2 (VDD), R1.5 (2), R1.6 (2), R1.7 (2), R1.8 (2), R10.1, U1.3 (WP#/IO2), U1.7 (HOLD#/IO3), U1.8 (VCC), U2.5 (OUT), U$3.19 (VDD_1), U$3.32 (VDD_2), U$3.42 (PA9/TIM1_CH2/USART1_TX(5T)), U$3.43 (PA10/TIM1_CH3/USART1_RX(5T)), U$3.48 (VDD_3), U$3.64 (VDD_4), X3.1 (VCC), X5.4 (SD_VDD)
A0: JP1.12, U$3.20 (PA4/ADC12_IN4)
A1: JP1.11, U$3.21 (PA5/ADC12_IN5)
A2: JP1.10, U$3.22 (PA6/ADC12_IN6(5T))
A3: JP1.9, U$3.23 (PA7/TIM1_CH1N/ADC12_IN7(FT))
A4: JP1.8, U$3.24 (PC4/ADC12_IN14)
A5: JP1.7, U$3.25 (PC5/ADC12_IN15)
AVCC: C13.1, C15.1, FB2.2, U$3.13 (VDDA)
BATTERY: TP3.P$1, U$3.1 (VBAT)
BOOT0: JP1.1, R4.1, U$3.60 (BOOT0)
CC1: R6.2, X6.A5 (CC1)
CC2: R5.2, X6.B5 (CC2)
D5: JP3.10, U$3.38 (PC7/TIM3_CH2/TIM8_CH2/USART6_RX(5T))
D6: JP3.9, U$3.37 (PC6/TIM3_CH1/TIM_CH1/USART6_TX(5T))
D8_NEOPIX: LED1.1 (DI), U$3.8 (PC0/ADC123_IN10(5T))
D9: JP3.8, U$3.61 (PB8/TIM10_CH1/TIM4_CH3(5T))
D10: JP3.7, U$3.62 (PB9/TIM11_CH1/TIM4_CH4(5T))
D11: JP3.6, U$3.11 (PC3/ADC123_IN13(5T))
D12: JP3.5, U$3.10 (PC2/ADC123_IN12(5T))
D13: JP3.4, R7.1, U$3.9 (PC1/ADC123_IN11(5T))
D+: D+0.TP, U$3.45 (PA12/CANTX/USBDP(5T)), X6.A6 (D+), X6.B6 (D+)
D-: D-0.TP, U$3.44 (PA11/TIM1_CH4/CANRX/USBDM(5T)), X6.A7 (D-), X6.B7 (D-)
EN: JP3.2, R3.1, U2.3 (EN)
FLASH_CS: R1.4 (1), U1.1 (SSEL), U$3.50 (PA15/JTDI(5T))
FLASH_MISO: U1.2 (MISO), U$3.56 (PB4/JNTRST(5T))
FLASH_MOSI: R9.4 (1), U1.5 (MOSI), U$3.57 (PB5(5T))
FLASH_SCK: U1.6 (SCK), U$3.55 (PB3/JTDO(5T))
GND: C1.2, C2.5 (2), C2.6 (2), C2.7 (2), C2.8 (2), C3.2, C4.2, C5.2, C6.2, C7.2, C8.2, C9.2, C10.2, C11.2, C12.2, C13.2, C14.2, C15.2, C16.2, C17.2, CONN1.1 (GND), CONN1.MT1 (MT), CONN1.MT2 (MT), JP1.13, L0.C, LED1.4 (GND), R4.2, R5.1, R6.1, R8.2, R9.3 (1), R9.5 (2), R9.7 (2), SW1.B (S), SW1.B' (S1), U1.4 (VSS), U2.2 (GND), U3.2 (VSS), U$3.12 (VSSA), U$3.18 (VSS_1), U$3.28 (PB2/BOOT1(5T)), U$3.63 (VSS_2), X1.1, X3.3 (GND@1), X3.5 (GND@2), X3.7 (KEY), X3.9 (GNDDETECT), X5.6 (GND@3), X5.CD1 (CARD_DETECT), X5.MT1 (GND@2), X5.MT2 (GND@1), X6.A1B12 (GND), X6.B1A12 (GND)
MISO: JP1.4, U$3.35 (PB14/SPI2_MISO(5T))
MOSI: JP1.5, U$3.36 (PB15/SPI2_MOSI(5T))
unnamed: CHG0.C, R2.1
unnamed: L0.A, R7.2
unnamed: R2.2, U3.1 (STAT)
unnamed: R8.1, U3.5 (PROG)
unnamed: C2.4 (1), U$3.3 (PC14/OSC32_IN(5T)), X2.P$1
unnamed: C2.2 (1), U$3.5 (PH0/OSC_IN(5T)), Y1.3 (2)
unnamed: C2.3 (1), U$3.4 (PC15/OSC32_OUT(5T)), X2.P$2
unnamed: C2.1, U$3.6 (PH1/OSC_OUT(5T)), Y1.1
RX_D0: JP1.3, R10.2, U$3.30 (PB11/I2C2_SDA(5T))
SCK: JP1.6, U$3.34 (PB13/SPI2_SCK(5T))
SCL: CONN1.4 (SCL), JP3.11, R1.2 (1), U$3.58 (PB6/I2C1_SCL/USART1_TX/TIM4_CH1(5T))
SDA: CONN1.3 (SDA), JP3.12, R1.1, U$3.59 (PB7/I2C1_SDA/USART1_RX/TIM4_CH2(5T))
SDIO_CLK: U$3.53 (PC12(5T)), X5.5 (SCLK)
SDIO_CMD: U$3.54 (PD2/TIM3_ETR(5T)), X5.3 (DATA_IN)
SDIO_D0: U$3.39 (PC8/TIM3_CH3/TIM8_CH3(5T)), X5.7 (DATA_OUT)
SDIO_D1: U$3.40 (PC9/TIM3_CH4/TIM8_CH4(5T)), X5.8 (DAT1)
SDIO_D2: U$3.51 (PC10(5T)), X5.1 (DAT2)
SDIO_D3: R1.3 (1), U$3.52 (PC11(5T)), X5.2 (CS)
SD_DETECT: U$3.33 (PB12(5T)), X5.CD2 (CARD_DETECT1)
SWCLK: TP2.P$1, U$3.49 (PA14/JTCK-SWCLK(5T)), X3.4 (SWDCLK)
SWDIO: TP1.P$1, U$3.46 (PA13/JTMS-SWDAT(5T)), X3.2 (SWDIO)
TX_D1: JP1.2, U$3.29 (PB10/I2C2_SCL(5T))
VBAT: C3.1, JP3.1, Q3.3 (D), R9.8 (2), U3.3 (VBAT), X1.2
VBUS: CHG0.A, D4.A, JP3.3, Q3.1 (G), R9.6 (2), U3.4 (VDD), X6.A4B9 (VBUS), X6.B4A9 (VBUS)
VCAP1: C9.1, U$3.31 (VCAP_1)
VCAP2: C12.1, U$3.47 (VCAP_2)
VHI: C6.1, D4.C, Q3.2 (S), R3.2, U2.1 (IN)
V_DIV: C17.1, R9.1, R9.2 (1), U$3.17 (PA3/ADC123_IN3(5T))
~RESET: C1.1, JP1.16, SW1.A, SW1.A' (P1), U$3.7 (NRST), X3.10 (NRESET)

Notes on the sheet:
BREAKOUTS
I2S2ext_SD
DACs
I2S2_SD
SPI2
USB AND BATTERY CHARGING
10K = 100mA
2.0K = 500mA
POWER AND FILTERING
RESET
5.0K = 200mA
I2S2_WS
RED LED
I2S2_BCLK
USART3
CAN
SPI1
1.0K = 1000mA
I2C1

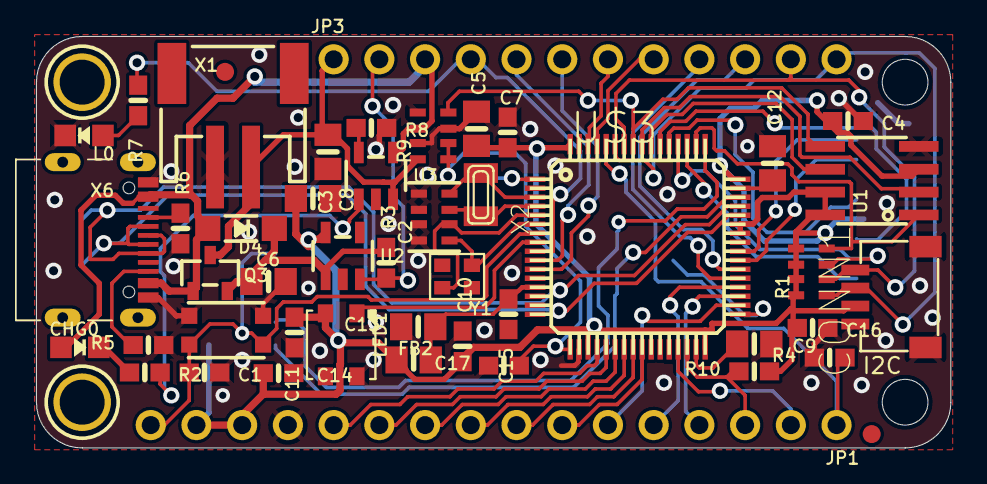
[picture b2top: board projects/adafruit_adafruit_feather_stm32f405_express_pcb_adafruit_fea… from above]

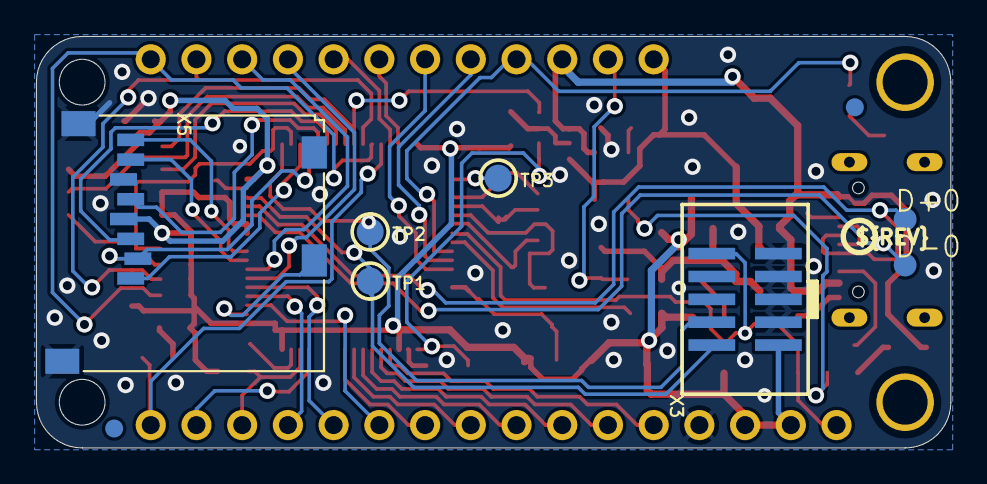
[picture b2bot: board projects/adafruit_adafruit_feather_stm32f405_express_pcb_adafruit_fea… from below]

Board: 2 copper layers, 50.8 x 22.9 mm, 63 parts (11 on the bottom side), 59 nets.

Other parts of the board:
@HOLE0, @HOLE1: (no value)
U$13: PCBFEAT-REV-040
U$24: FEATHER_STM32F405_TOP
U$40: FEATHER_STM32F405_BOT

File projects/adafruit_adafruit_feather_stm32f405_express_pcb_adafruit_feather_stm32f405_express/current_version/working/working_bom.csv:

"Id";"Designator";"Footprint";"Quantity";"Designation";"Supplier and ref";
1;"C5";"0805-NO";1;"10uF";;;
2;"R2";"0603-NO";1;"1K";;;
3;"C12,C13,C3,C9,C8,C6";"0805-NO";6;"10µF";;;
4;"L0";"CHIPLED_0805_NOOUTLINE";1;"RED";;;
5;"C7,C16,C11,C10,C4,C14,C17";"0603-NO";7;"1uF";;;
6;"SW1";"BTN_KMR2_4.6X2.8";1;"KMR2";;;
7;"R5,R8,R6";"0603-NO";3;"5.1K";;;
8;"U1";"SOIC8_150MIL";1;"25Q16";;;
9;"X1";"JSTPH2";1;"JSTPH";;;
10;"U$24";"FEATHER_STM32F405_TOP";1;"";;;
11;"U2";"SOT23-5";1;"AP2112-3.3";;;
12;"FB2";"0805-NO";1;"ferrite";;;
13;"U$32,U$31";"MOUNTINGHOLE_2.5_PLATED";2;"MOUNTINGHOLE2.5";;;
14;"Q3";"SOT23-R";1;"DMG3405";;;
15;"U$35,U$34,U$37,U$5";"FIDUCIAL_1MM";4;"FIDUCIAL_1MM";;;
16;"R7";"0603-NO";1;"2.2K";;;
17;"X6";"USB_C_CUSB31-CFM2AX-01-X";1;"";;;
18;"JP1";"1X16_ROUND";1;"";;;
19;"R3";"0603-NO";1;"10K";;;
20;"C15,C1";"0603-NO";2;"0.1uF";;;
21;"C2";"RESPACK_4X0603";1;"22pF";;;
22;"JP3";"1X12_ROUND";1;"";;;
23;"CHG0";"CHIPLED_0805_NOOUTLINE";1;"ORANGE";;;
24;"R4,R10";"0603-NO";2;"100K";;;
25;"Y1";"CRYSTAL_2.5X2";1;"12mhz";;;
26;"CONN1";"JST_SH4";1;"STEMMA_I2C_QT";;;
27;"U$3";"TQFP64";1;"STM32F405R";;;
28;"R1";"RESPACK_4X0603_NO";1;"10K";;;
29;"@HOLE1,@HOLE0";"";2;"";;;
30;"LED1";"LED3535";1;"WS2812B3535";;;
31;"X2";"XTAL3215";1;"32.768";;;
32;"R9";"RESPACK_4X0603_NO";1;"100K";;;
33;"U3";"SOT23-5";1;"MCP73831T-2ACI/OT";;;
34;"D4";"SOD-123";1;"MBR054";;;
35;"D+0,D-0";"B1,27";2;"TPB1,27";;;
36;"X5";"MICROSD";1;"";;;
37;"TP1,TP3,TP2";"TESTPOINT_ROUND_1.5MM";3;"";;;
38;"U$13";"PCBFEAT-REV-040";1;"";;;
39;"U$40";"FEATHER_STM32F405_BOT";1;"";;;
40;"X3";"2X05_1.27MM_SMT";1;"";;;
